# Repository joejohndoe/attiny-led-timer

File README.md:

# ATtiny LED Timer

A timer circuit that switches an LED light (like an LED string) on a fixed daily schedule. The circuit is designed to be battery-powered and thus optimized for power efficiency. 

A 14-pin Microchip tinyAVR 1 MCU (e.g. ATtiny414) keeps time with a 32.768 kHz watch crystal with < 2s drift per day. It spends most of the time in power-down sleep, resulting in a low 4 µA average current draw for the MCU. A PAM2804 constant-current buck driver powers the LED. The circuit is designed for two separate power rails: a CR1220/CR1225 coin cell for the MCU and an external Li-Ion battery pack for the LEDs, chargeable via a DC power jack. This split allows the MCU to keep the time while the battery pack is charging, without any risk of interference.

Other features:
- **Low-voltage cutoff:** the LED switches off when the battery pack drops below 3.0 V to keep the LED driver stable and prolong battery life. **It is still recommended to use a battery pack with undervoltage protection!**
- **One-button control:** manual override, battery voltage readout and schedule re-sync.
- **Current-measurement jumpers** for the MCU and LED supplies, so you can profile power draw. Insert bridges if you don't need it.
- **Additional GPIO pins** PB0 and PB1 available on the board for auxiliary use.

|  |  |
|-|-|

## Hardware

Schematic and PCB are available in `hardware/attiny-led-timer.kicad_pro` in KiCad 10 format.

### LED Driver

The LED driver is built for LEDs with a forward voltage of 2.7V. The current can be set via sense resistor R1. A resistance of 1.65 Ohms results in a current of roughly 60 mA - see below for instructions on how to compute the resistor value. The LEDs are powered by a power source of 3-6 V wired to the BAT+/- pads. I'm using three 18650 Li-Ion batteries in parallel, which last for roughly 170 h of LED on-time, i.e. about 16 days with the default schedule (10.5 h on per day). The DC power jack connector can be used to charge the batteries (with an appropriate charger). It switches BAT- away from the circuit's GND when connected to isolate the circuit during charging - this means you can't power the LEDs from the DC connector directly (unless you short the ground switch).

#### Adapting to your LED light

The current flowing through the LED output is determined by the value of the sense resistor, R1. The PAM2804 regulates the voltage across R1 to its feedback voltage of 0.1 V, so:

```
R1 = 0.1 V / I_LED        I_LED = 0.1 V / R1
```

To match it to your LEDs, first measure the forward voltage (voltage drop across the two leads when powered) of the LEDs. It should be lower than the supply voltage by some margin. Otherwise, the LED driver won't be able to provide the chosen current, and thus the LEDs will be dimmer than intended. 

Then measure the current draw of the LEDs, or determine the desired current (-> brightness) with a bench power supply in CC mode. Calculate the sense resistor value using the above formula. 

The constant current approach is most appropriate for LED lights that don't already have a current-limiting resistor built in. LED strips (the flat kind with adhesive tape on the back) often come with current-limiting resistors. You could still use the circuit at hand to control the brightness/power consumption, but the power loss across the resistors will limit the overall efficiency.

### Controller

The circuit and code works with any of the 14-pin microcontrollers of the Microchip tinyAVR 1 family: from ATtiny214 to ATtiny3214. The code fits into the ATtiny414 and up (about 2.1 KB of flash). It is slightly too big for the 2 KB of the ATtiny214, but can be made to fit, e.g. by replacing `attachInterrupt()` with a direct pin-change ISR.

The MCU is powered by a coin cell so it doesn't lose time even when the main power source is disconnected (e.g. for charging). It is clocked at 1 MHz, so the voltage can go down to 1.8V. The MCU only consumes ~4 uA on average, which means that a CR1220 coin cell can power it for up to a year.

There is a status LED and a button wired to the MCU. Both are entirely optional, not needed for regular use.

### Board and parts

The board measures about 47 × 31 mm and has three M2.5 mounting holes. All resistors and capacitors use a 0805 footprint.

| Ref | Part | Package | Purpose |
|-----|------|---------|---------|
| U1 | ATtiny1614 (or another 14-pin tinyAVR 1-series MCU) | SOIC-14 | Microcontroller |
| Y1 | 32.768 kHz crystal (e.g. ECS-.327-12.5-13X) | Cylindrical, horizontal | RTC time base |
| C2, C3 | 18 pF | 0805 | Crystal load capacitors |
| C1 | 100 nF | 0805 | MCU decoupling |
| BT1 | Keystone 1056 coin cell holder (CR1220/CR1225) | SMD | MCU supply |
| U2 | PAM2804 | TSOT-23-5 | Step-down constant-current LED driver |
| L1 | 2.2 µH (e.g. Samsung CIGT201610EH2R2MNE) | 2016 (2.0 × 1.6 mm) | Buck inductor |
| R1 | 1.65 Ω | 0805 | LED current sense (see [above](#computing-the-sense-resistor-value)) |
| C4 | 10 µF | 0805 | LED driver input capacitor |
| C5 | 10 µF | 0805 | LED driver output capacitor |
| R2, R3 | 1 MΩ | 0805 | Battery voltage divider |
| C6 | 10 nF | 0805 | Voltage divider filter |
| SW1 | 6 mm tactile switch | THT | Control button |
| D2 | LED | 0805 | Status LED |
| R4 | 10 kΩ | 0805 | Status LED resistor |
| J1 | DC barrel jack (PJ-079BH) | THT | Charging input; disconnects BAT− from GND while a plug is inserted |
| BAT+, BAT− | – (solder pads) | – | LED battery pack |
| J2 | JST-PH 2-pin, horizontal (S2B-PH-K) | THT | LED output |
| J3 | 1×5 pin header, 2.54 mm | THT | Programming / data header: GND, VDD, UPDI, PB0, PB1 |
| J7 | 1×2 pin header + jumper | THT | Isense1: MCU supply. Fit a jumper, or connect an ammeter to measure current |
| J4 | 1×2 pin header + jumper | THT | Isense2: LED supply. Fit a jumper, or connect an ammeter to measure current |

## Firmware

The firmware is written as an Arduino sketch in `src/led_timer/led_timer.ino`. You can configure the exact on/off times in `kPhaseEnds[]`, and the battery voltage cutoff with  `kLowVoltageThresholdMv` / `kRecoveryVoltageMv` if needed.

### Requirements

- [Arduino IDE](https://www.arduino.cc/en/software)
- [megaTinyCore](https://github.com/SpenceKonde/megaTinyCore) board package
- A UPDI programmer (see below)

### Building and flashing

The MCU is flashed via UPDI. I'm using Adafruit's UPDI Friend, but there are cheaper solutions like [SerialUPDI](https://github.com/SpenceKonde/AVR-Guidance/blob/master/UPDI/jtag2updi.md). Note that there's no resistor between the UPDI connector and the MCU on this board, as I found it to be unnecessary with the UPDI Friend.

Configure the following settings in Arduino IDE:
1. Select **Tools → Board → megaTinyCore → ATtiny3224/1624/1614/1604/824/814/804/424/414/404/214/204**
2. Set **Tools → Chip** to **ATtiny1614**.
3. Set **Tools → Clock** to **1 MHz internal**.
4. Set **Tools → Programmer** according to the programmer you're using (**SerialUPDI - SLOW: 57600 baud** for the UPDI Friend) and select the right port for **Tools → Port**.

### Usage

| Action | Effect | Feedback (status LED) |
|--------|--------|-----------------------|
| Power up | Starts the clock at 8 PM | 3 blinks |
| **Short press** | Toggles the override: inverts the LED state until the next phase change | 2 blinks = LED now on, 1 blink = LED now off |
| **Double press** | Measures the LED battery pack and blinks out its voltage | See below |
| **Long press** (2 s) | Resets the clock to 8 PM and clears the override | 3 blinks |

Voltage readout: the voltage is blinked as three digits, with a 1 s pause before each one.
For example, 3.75 V is shown as 3 blinks, 7 blinks, then 5 blinks. A zero is shown as 10 quick blinks. Use this to verify that the battery voltage readout is still correct after making changes to the voltage sense circuitry.

To sync the MCU's time with the real time, long-press the button at 8 PM.

### How it works

At startup, the input buffers on every pin are disabled to avoid leakage from floating inputs. The button
pin is then re-enabled with a pull-up and a wake-up interrupt. The RTC's periodic interrupt timer (PIT) fires once per
second from the crystal and increments a seconds counter. Each time the MCU wakes up, it:

1. handles a button press, if there is one,
2. samples the LED battery pack voltage (the ADC is only enabled for a few hundred µs),
3. works out the current schedule phase and drives the LED driver's enable pin,
4. goes back to power-down sleep.

## License

Released under the [MIT License](LICENSE). This covers everything in this repository: the firmware in `src/`,
the KiCad design files in `hardware/` and the images in `docs/`.

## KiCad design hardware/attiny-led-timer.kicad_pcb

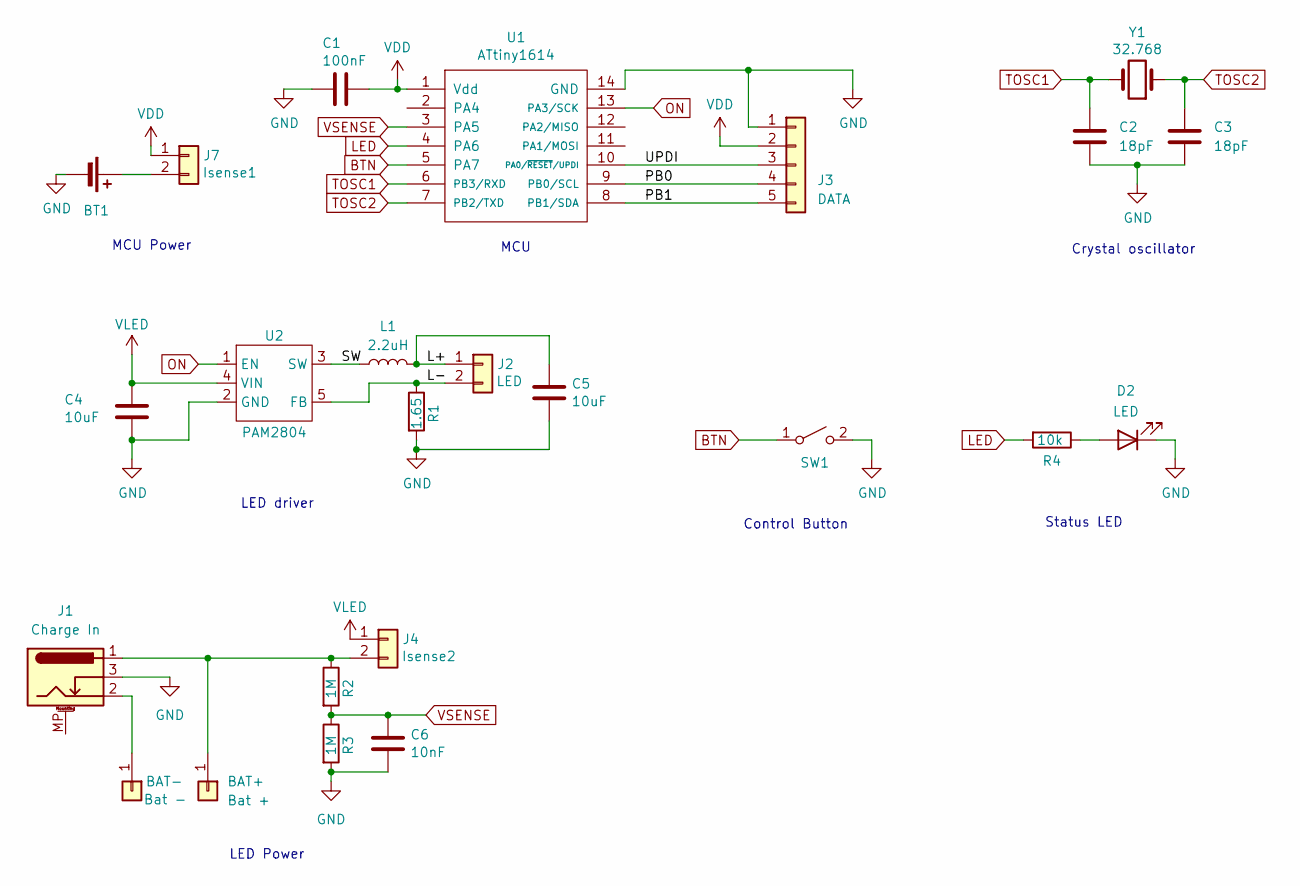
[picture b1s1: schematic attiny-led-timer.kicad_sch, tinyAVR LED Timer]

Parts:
BAT+: Bat +; SolderWirePad_1x01_SMD_3x6mm
BAT-: Bat -; SolderWirePad_1x01_SMD_3x6mm
BT1: Battery_Cell; BatteryHolder_Keystone_1056
C1: 100nF; 0805_HandSolder
C2, C3: 18pF; 0805_HandSolder
C4, C5: 10uF; 0805_HandSolder
C6: 10nF; 0805_HandSolder
D2: LED; 0805_HandSolder
J1: Charge In; BarrelJack_PJ-079BH
J2: LED; JST_PH_S2B-PH-K_1x02_P2.00mm_Horizontal
J3: DATA; PinHeader_1x05_P2.54mm_Vertical
J4: Isense2; PinHeader_1x02_P2.54mm_Vertical
J7: Isense1; PinHeader_1x02_P2.54mm_Vertical
L1: 2.2uH; INDC2016X100N
R1: 1.65; 0805_HandSolder
R2, R3: 1M; 0805_HandSolder
R4: 10k; 0805_HandSolder
SW1: SW_PUSH_6mm
U1: ATtiny1614; SOIC-14_3.9x8.7mm_P1.27mm_HandSolder
U2: PAM2804; TSOT-23-5
Y1: 32.768; Crystal_C26-LF_D2.1mm_L6.5mm_Horizontal

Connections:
/L+: C5.1, J2.1, L1.2
/L-: J2.2, R1.1, U2.5 (FB)
/PB0: J3.4, U1.9 (PB0/SCL)
/PB1: J3.5, U1.8 (PB1/SDA)
/SW: L1.1, U2.3 (SW)
/UPDI: J3.3, U1.10 (PA0/~RESET/UPDI)
BTN: SW1.1 (A), U1.5 (PA7)
GND: BT1.2 (-), C1.2, C2.2, C3.2, C4.2, C5.2, C6.2, D2.1 (K), J1.3, J3.1, R1.2, R3.2, SW1.2 (B), U1.14 (GND), U2.2 (GND)
LED: R4.2, U1.4 (PA6)
unnamed: BAT+.1, J1.1, J4.2, R2.1
unnamed: BAT-.1, J1.2
unnamed: BT1.1 (+), J7.2
unnamed: D2.2 (A), R4.1
ON: U1.13 (PA3/SCK), U2.1 (EN)
TOSC1: C2.1, U1.6 (PB3/RXD), Y1.2
TOSC2: C3.1, U1.7 (PB2/TXD), Y1.1
VDD: C1.1, J3.2, J7.1, U1.1 (Vdd)
VLED: C4.1, J4.1, U2.4 (VIN)
VSENSE: C6.1, R2.2, R3.1, U1.3 (PA5)

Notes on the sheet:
LED driver
MCU Power
Status LED
LED Power
Crystal oscillator
Control Button
MCU

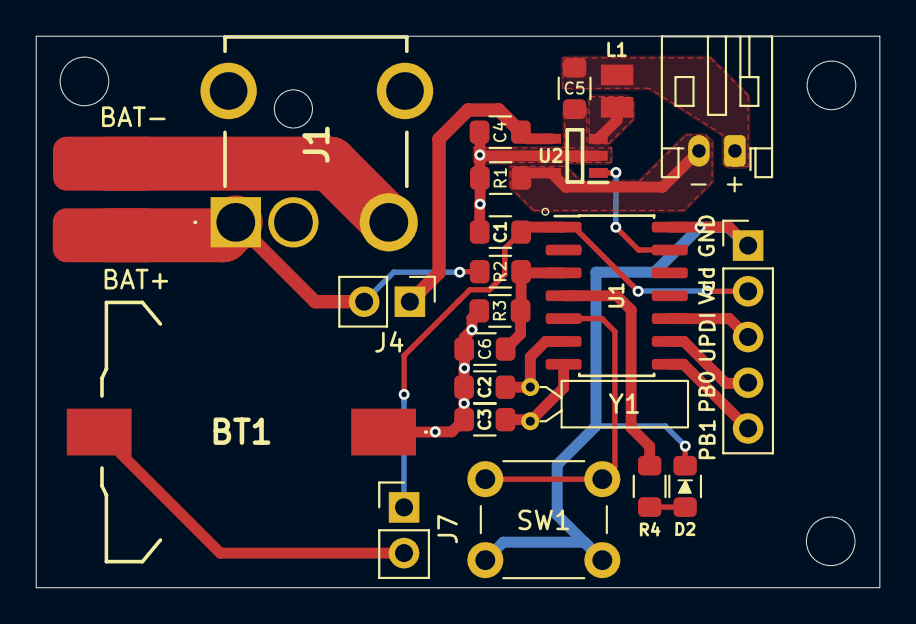
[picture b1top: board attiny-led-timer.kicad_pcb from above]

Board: 2 copper layers, 46.9 x 30.6 mm, 27 parts (0 on the bottom side), 19 nets.

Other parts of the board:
H1, H2, H3: MountingHole; MountingHole_2.7mm_M2.5_ISO14580

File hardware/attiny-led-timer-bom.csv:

"Reference","Value","Footprint","QUANTITY"
"BT1","Battery_Cell","attiny-led-timer:BatteryHolder_Keystone_1056","1"
"C1","100nF","attiny-led-timer:0805_HandSolder","1"
"C2,C3","18pF","attiny-led-timer:0805_HandSolder","2"
"C4,C5","10uF","attiny-led-timer:0805_HandSolder","2"
"C6","10nF","attiny-led-timer:0805_HandSolder","1"
"D2","LED","attiny-led-timer:0805_HandSolder","1"
"J1","Charge In","attiny-led-timer:BarrelJack_PJ-079BH","1"
"J2","LED","Connector_JST:JST_PH_S2B-PH-K_1x02_P2.00mm_Horizontal","1"
"J3","DATA","Connector_PinHeader_2.54mm:PinHeader_1x05_P2.54mm_Vertical","1"
"J4","Isense2","Connector_PinHeader_2.54mm:PinHeader_1x02_P2.54mm_Vertical","1"
"J7","Isense1","Connector_PinHeader_2.54mm:PinHeader_1x02_P2.54mm_Vertical","1"
"L1","2.2uH","attiny-led-timer:INDC2016X100N","1"
"R1","1.65","attiny-led-timer:0805_HandSolder","1"
"R2,R3","1M","attiny-led-timer:0805_HandSolder","2"
"R4","10k","attiny-led-timer:0805_HandSolder","1"
"SW1","","Button_Switch_THT:SW_PUSH_6mm","1"
"U1","ATtiny1614","attiny-led-timer:SOIC-14_3.9x8.7mm_P1.27mm_HandSolder","1"
"U2","PAM2804","attiny-led-timer:TSOT-23-5","1"
"Y1","32.768","Crystal:Crystal_C26-LF_D2.1mm_L6.5mm_Horizontal","1"

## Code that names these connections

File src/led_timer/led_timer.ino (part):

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#include <avr/sleep.h>

// Pin definitions
const int kStatusLedPin = PIN_PA6; 
const int kButtonPin = PIN_PA7;
const int kLedDriverPin = PIN_PA3;
const int kVoltageSensePin = PIN_PA5;

// Times of day, in seconds since midnight
const uint32_t kMinute = 60UL;
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
// --- Voltage sensing ---

// Reads PA5 through the 1M/1M divider (with 10nF filter cap) and returns the
// estimated Vin in millivolts.
//
// The ADC uses VDD (the coin cell) as its reference, and the internal 1.1V
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

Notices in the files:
hardware/attiny-led-timer.kicad_pcb:
License: MIT
